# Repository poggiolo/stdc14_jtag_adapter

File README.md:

# STDC14 to JTAG 14 Adapter board

Created to adapt STLINKV3-MINIE STDC14 connector to a more common JTAG 2.54mm header.

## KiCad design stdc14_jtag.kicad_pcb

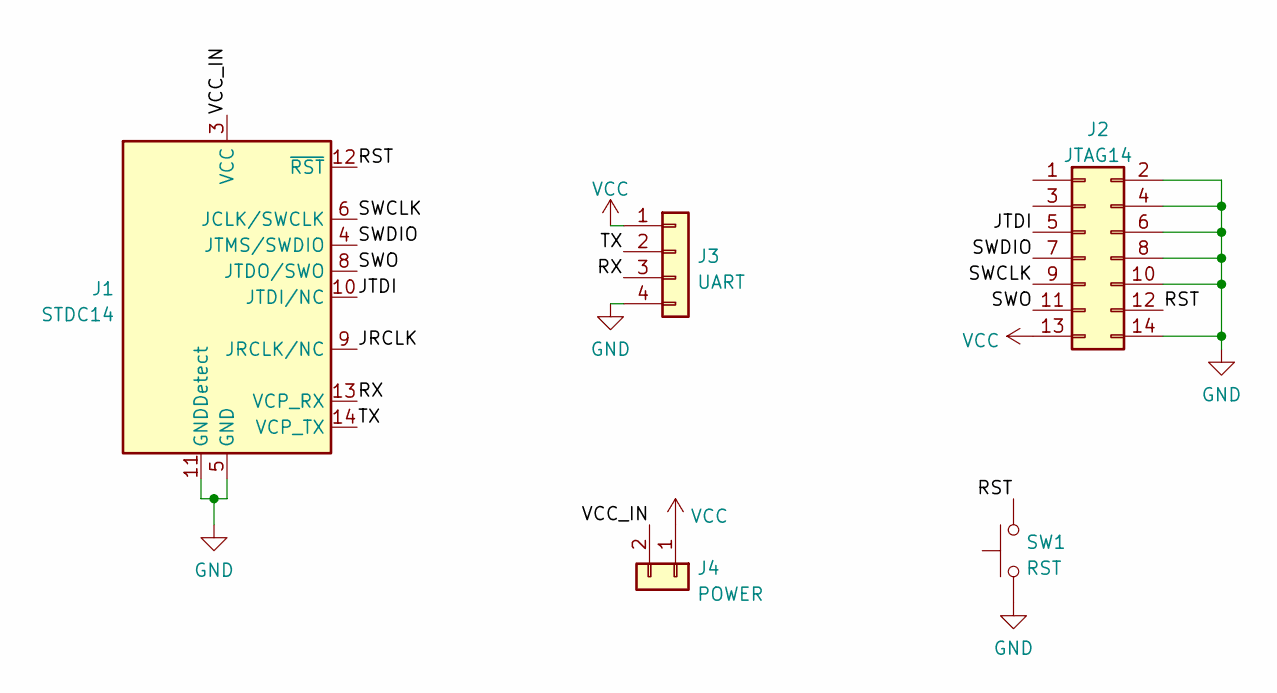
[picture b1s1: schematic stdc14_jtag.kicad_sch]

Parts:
J1: STDC14; PinSocket_1x04_P2.54mm_Vertical
J2: JTAG14; IDC-Header_2x07_P2.54mm_Vertical
J3: UART; PinSocket_1x04_P2.54mm_Vertical
J4: POWER; PinHeader_1x02_P2.54mm_Vertical
SW1: RST; SW_PUSH_6mm

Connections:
/JRCLK: J1.9 (JRCLK/NC)
/JTDI: J1.10 (JTDI/NC), J2.5
/RST: J1.12 (~RST), J2.12, SW1.2
/RX: J1.13 (VCP_RX), J3.3
/SWCLK: J1.6 (JCLK/SWCLK), J2.9
/SWDIO: J1.4 (JTMS/SWDIO), J2.7
/SWO: J1.8 (JTDO/SWO), J2.11
/TX: J1.14 (VCP_TX), J3.2
/VCC_IN: J1.3 (VCC), J4.2
GND: J1.5 (GND), J1.7 (GND), J1.11 (GNDDetect), J2.2, J2.4, J2.6, J2.8, J2.10, J2.14, J3.4, SW1.1
VCC: J2.13, J3.1, J4.1

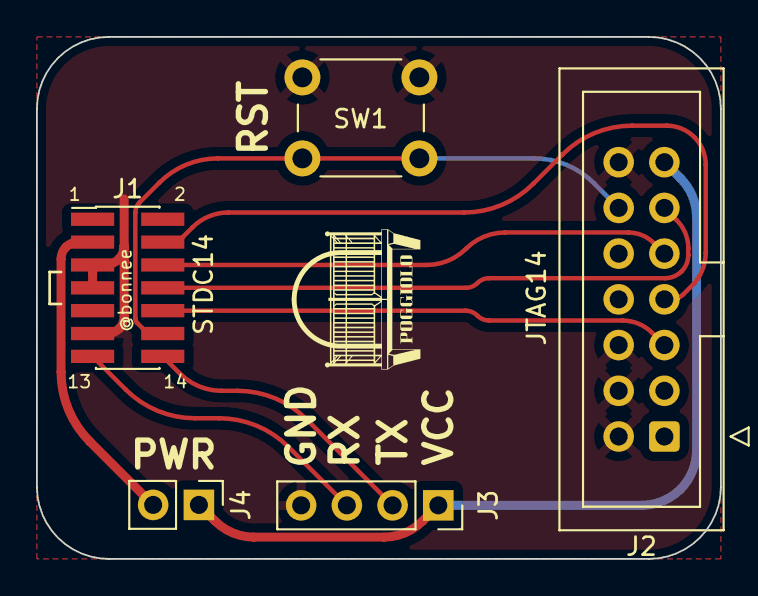
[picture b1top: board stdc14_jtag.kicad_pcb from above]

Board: 2 copper layers, 38.0 x 29.0 mm, 5 parts (0 on the bottom side), 10 nets.

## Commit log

2022-12-19 Add license
2022-12-19 fix: solve bottom silkscreen legend errors
2022-12-20 feat: replace OSHW symbol with Frullino
2022-12-20 chore: thicken power lines
2022-12-22 Add external libs and modules
2022-12-22 feat: add front ground plane
2022-12-30 Fix uart legends
